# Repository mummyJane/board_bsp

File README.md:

# board_bsp

Board Support Packages (BSPs), test firmware, documentation and KiCad schematics
for a family of ESP32-P4 based boards.

Current version: see [VERSION](VERSION) · History: see [CHANGELOG.md](CHANGELOG.md)

## Boards

| Board | Folder | Status |
|-------|--------|--------|
| Waveshare ESP32-P4-WIFI6-Touch-LCD-7B-C (reference / test board) | [boards/esp32-p4-wifi6-touch-lcd-7b](boards/esp32-p4-wifi6-touch-lcd-7b/) | Bring-up |
| ADSB_Test — ESP32-P4 ADS-B test board derived from the above | [boards/adsb-test](boards/adsb-test/) | Rev A design (requirements / architecture) |

The Waveshare board is used to develop and validate the BSP and test code. The
next (custom) board reuses its design as a starting point, so everything proven
on the reference board should carry over with only pin/peripheral changes.

## Repository layout

```
board_bsp/
├── VERSION                 Project version (SemVer)
├── CHANGELOG.md            All notable changes, newest first
├── docs/                   Project-wide docs (setup, conventions)
├── common/components/      ESP-IDF components shared by all boards
└── boards/
    ├── _template/          Starting point for a new board
    └── <board>/
        ├── README.md       Board summary, pin map, status
        ├── bsp/            ESP-IDF BSP component for the board
        ├── test/           ESP-IDF test application (hardware bring-up tests)
        ├── docs/           Datasheets notes, bring-up logs, errata
        └── hardware/       KiCad project (schematic / PCB)
```

## Reference documents

Datasheets and links for every part: [docs/datasheets.md](docs/datasheets.md).
Run `python tools/fetch_datasheets.py` to download the PDFs into `datasheets/`
(git-ignored; vendor documents aren't redistributed in this public repo).

## Manufacturing

PCBs and assembly by PCBWay: capabilities, design rules and the hand-solder policy are in
[docs/pcb-manufacturing.md](docs/pcb-manufacturing.md).

## Toolchain

- **Firmware:** ESP-IDF v6.1 (ESP32-P4 target) — see [docs/setup.md](docs/setup.md)
- **Hardware:** KiCad 10

## Quick start (test app)

```powershell
. .\tools\idf_env.ps1     # load ESP-IDF v6.1
cd boards\esp32-p4-wifi6-touch-lcd-7b\test
idf.py set-target esp32p4
idf.py build flash monitor
```

## Versioning

See [docs/versioning.md](docs/versioning.md).

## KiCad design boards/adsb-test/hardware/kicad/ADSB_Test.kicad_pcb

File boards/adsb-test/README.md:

# ADSB_Test

ESP32-P4 based ADS-B test board, derived from the Waveshare
ESP32-P4-WIFI6-Touch-LCD-7B-C reference board. It is kept as close to the
reference board as possible, so firmware and circuits can be proven on the
reference board while ADSB_Test is designed.

**Hardware revision:** Rev A (design started 2026-10-09). **Status:** requirements / architecture draft.

## Features

- **OSPTEK ESP32-P4C5 Core** module: ESP32-P4 (rev v3) + ESP32-C5 (dual-band Wi-Fi 6 backup link over SDIO, esp_hosted, same wiring as the reference board's C6), 16 MB flash, 32 MB PSRAM, IPEX antenna; 1.0 mm stamp holes
- P4 RTC on the always-on backup supply (optional DS3231M, not fitted by default)
- **ADSBee m1421** dual-band ADS-B receiver (1090 MHz Mode S + 978 MHz UAT), RF front end copied from the ADSBee 1421 carrier
- 10/100 Ethernet (LAN8720A RMII PHY, HR911105A RJ45 MagJack)
- **User USB-C:** USB-PD sink (main power + charging) and a USB-UART to the P4 user UART
- **Dev USB-C:** one cable for all debug: P4 USB-Serial/JTAG, P4 + C5 UARTs with auto-reset (FT2232H), m1421 console + firmware upload (RP2040 with ADSBee 1421 Programmer firmware). m1421 JTAG on a J-Link header
- **USB-A host** (P4 USB 2.0 HS) to an external hub: 1 SDR (AIS etc.), 2 supported, 4 nice-to-have
- GNSS module with PPS
- ≈ 188 × 97 mm board (screen + 12 mm margins on the short edges) with the 7" EK79007 panel bonded to its top side (Waveshare stack-up, all parts on the bottom). 3D-printed plastic case, thicker long walls Digital connectors on one edge; GNSS and ADS-B SMA connectors on the opposite edge, with optional RF cans
- 2S1P 18650 Li-ion (≥ 1 h with everything running), buck-boost charger with power path
- Voltage + current monitoring on every rail (3 × PAC1954, 12 channels)
- Same 7" 1024×600 MIPI-DSI display and touch as the reference board
- microSD (kept from the reference board). Audio, CAN, RS485 and camera dropped
- Test points on every rail, and a 2×20 keyed header for the **Kingst LA5016** cable: 16 key digital signals + PWM outputs. Second row reserved for an LA5032

## Documents

| Doc | Content |
|-----|---------|
| [docs/requirements.md](docs/requirements.md) | Numbered requirements and how each is tested before hardware exists |
| [docs/architecture.md](docs/architecture.md) | Block diagram, power tree, monitor channel map, USB topology, GPIO budget, risks, proposed parts |
| [docs/open-questions.md](docs/open-questions.md) | Decisions waiting on an answer |
| [docs/test-plan.md](docs/test-plan.md) | Phase 1 (reference board + eval boards) and Phase 2 (ADSB_Test) tests |
| [docs/bringup-log.md](docs/bringup-log.md) | Test results |

## Folders

| Folder | Content |
|--------|---------|
| [bsp/](bsp/) | ESP-IDF BSP component. Pin map in [board_pins.h](bsp/include/bsp/board_pins.h) |
| [test/](test/) | Test app (Unity menu) |
| [hardware/kicad/](hardware/kicad/) | KiCad 10 project `ADSB_Test.kicad_pro`. One hierarchical sheet per block, each holding its design notes. Project library in [lib/](hardware/kicad/lib/) (m1421 symbol + footprint) |

## KiCad sheets

| Page | Sheet | Contents |
|------|-------|----------|
| 1 | Top level | — |
| 2 | Power Input | User USB-C, STUSB4500 PD sink, input protection |
| 3 | Charger Battery | BQ25798 2S charger, pack connector, VBACKUP |
| 4 | Power Rails | 5 V / 3V3 bucks, POWER switch, shunts, load switches |
| 5 | Power Monitor | 3 x PAC1954 |
| 6 | MCU Module | OSPTEK ESP32-P4C5 Core (ESP32-P4 + ESP32-C5) |
| 7 | RTC | DS3231M on VBACKUP (optional, DNP) |
| 8 | Ethernet | LAN8720A + HR911105A |
| 9 | USB User | CP2102N -> P4 UART1 |
| 10 | Dev USB Hub | Dev USB-C, USB2514B hub, 3V3_DEV regulator |
| 11 | USB Host | TPS259621 eFuse, USB-A |
| 12 | GPS | MAX-M10S, active antenna, SMA |
| 13 | Display Touch | Panel supplies (as reference board), LCD + touch FPCs |
| 14 | M1421 | ADSBee m1421, Dev Kit header, JTAG, RF combiner, SMA |
| 15 | Storage Misc | microSD, TCA6408A expander |
| 16 | Test Debug | LA5016 header, PWM pads, mounting holes |
| 17 | Dev UARTs | FT2232H (P4 + C5 consoles, auto-reset), UART buffers |
| 18 | Dev m1421 Programmer | RP2040 + flash (stock ADSBee Programmer), m1421 buffers, GPIO header |

All sheets are generated by the scripts in [hardware/gen/](hardware/gen/) (whole-project ERC: 0 violations).

**Bill of materials:** [hardware/bom/ADSB_Test_BOM.md](hardware/bom/ADSB_Test_BOM.md), with manufacturer part
numbers, DigiKey/LCSC codes and order links, plus a DigiKey upload file. Rebuild with
`python boards/adsb-test/hardware/bom/make_bom.py --boards N`.

## Hardware revisions

| Rev | Date | Changes |
|-----|------|---------|
| A | — | In design |

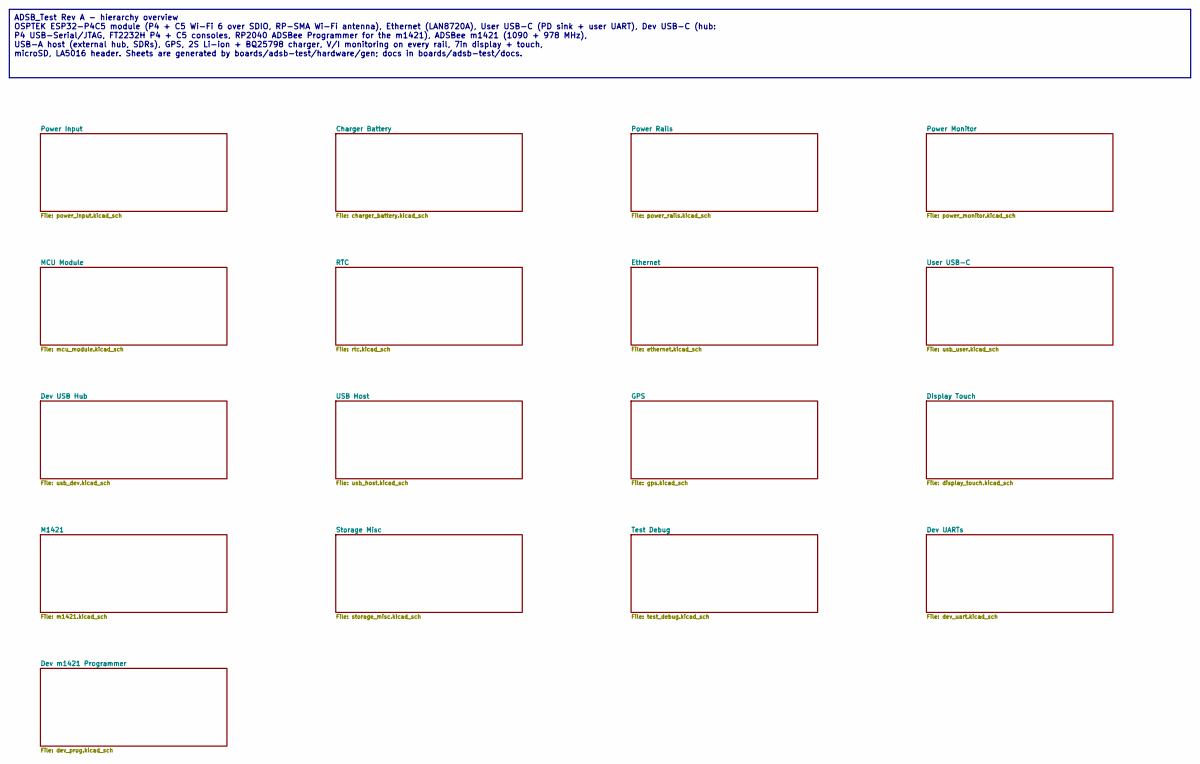
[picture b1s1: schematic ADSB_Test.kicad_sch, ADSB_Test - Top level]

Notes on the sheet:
ADSB_Test Rev A - hierarchy overview OSPTEK ESP32-P4C5 module (P4 + C5 Wi-Fi 6 over SDIO, RP-SMA Wi-Fi antenna), Ethernet (LAN8720A), User USB-C (PD sink + user UART), Dev USB-C (hub: P4 USB-Serial/JTAG, FT2232H P4 + C5 consoles, RP2040 ADSBee Programmer for the m1421), ADSBee m1421 (1090 + 978 MHz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

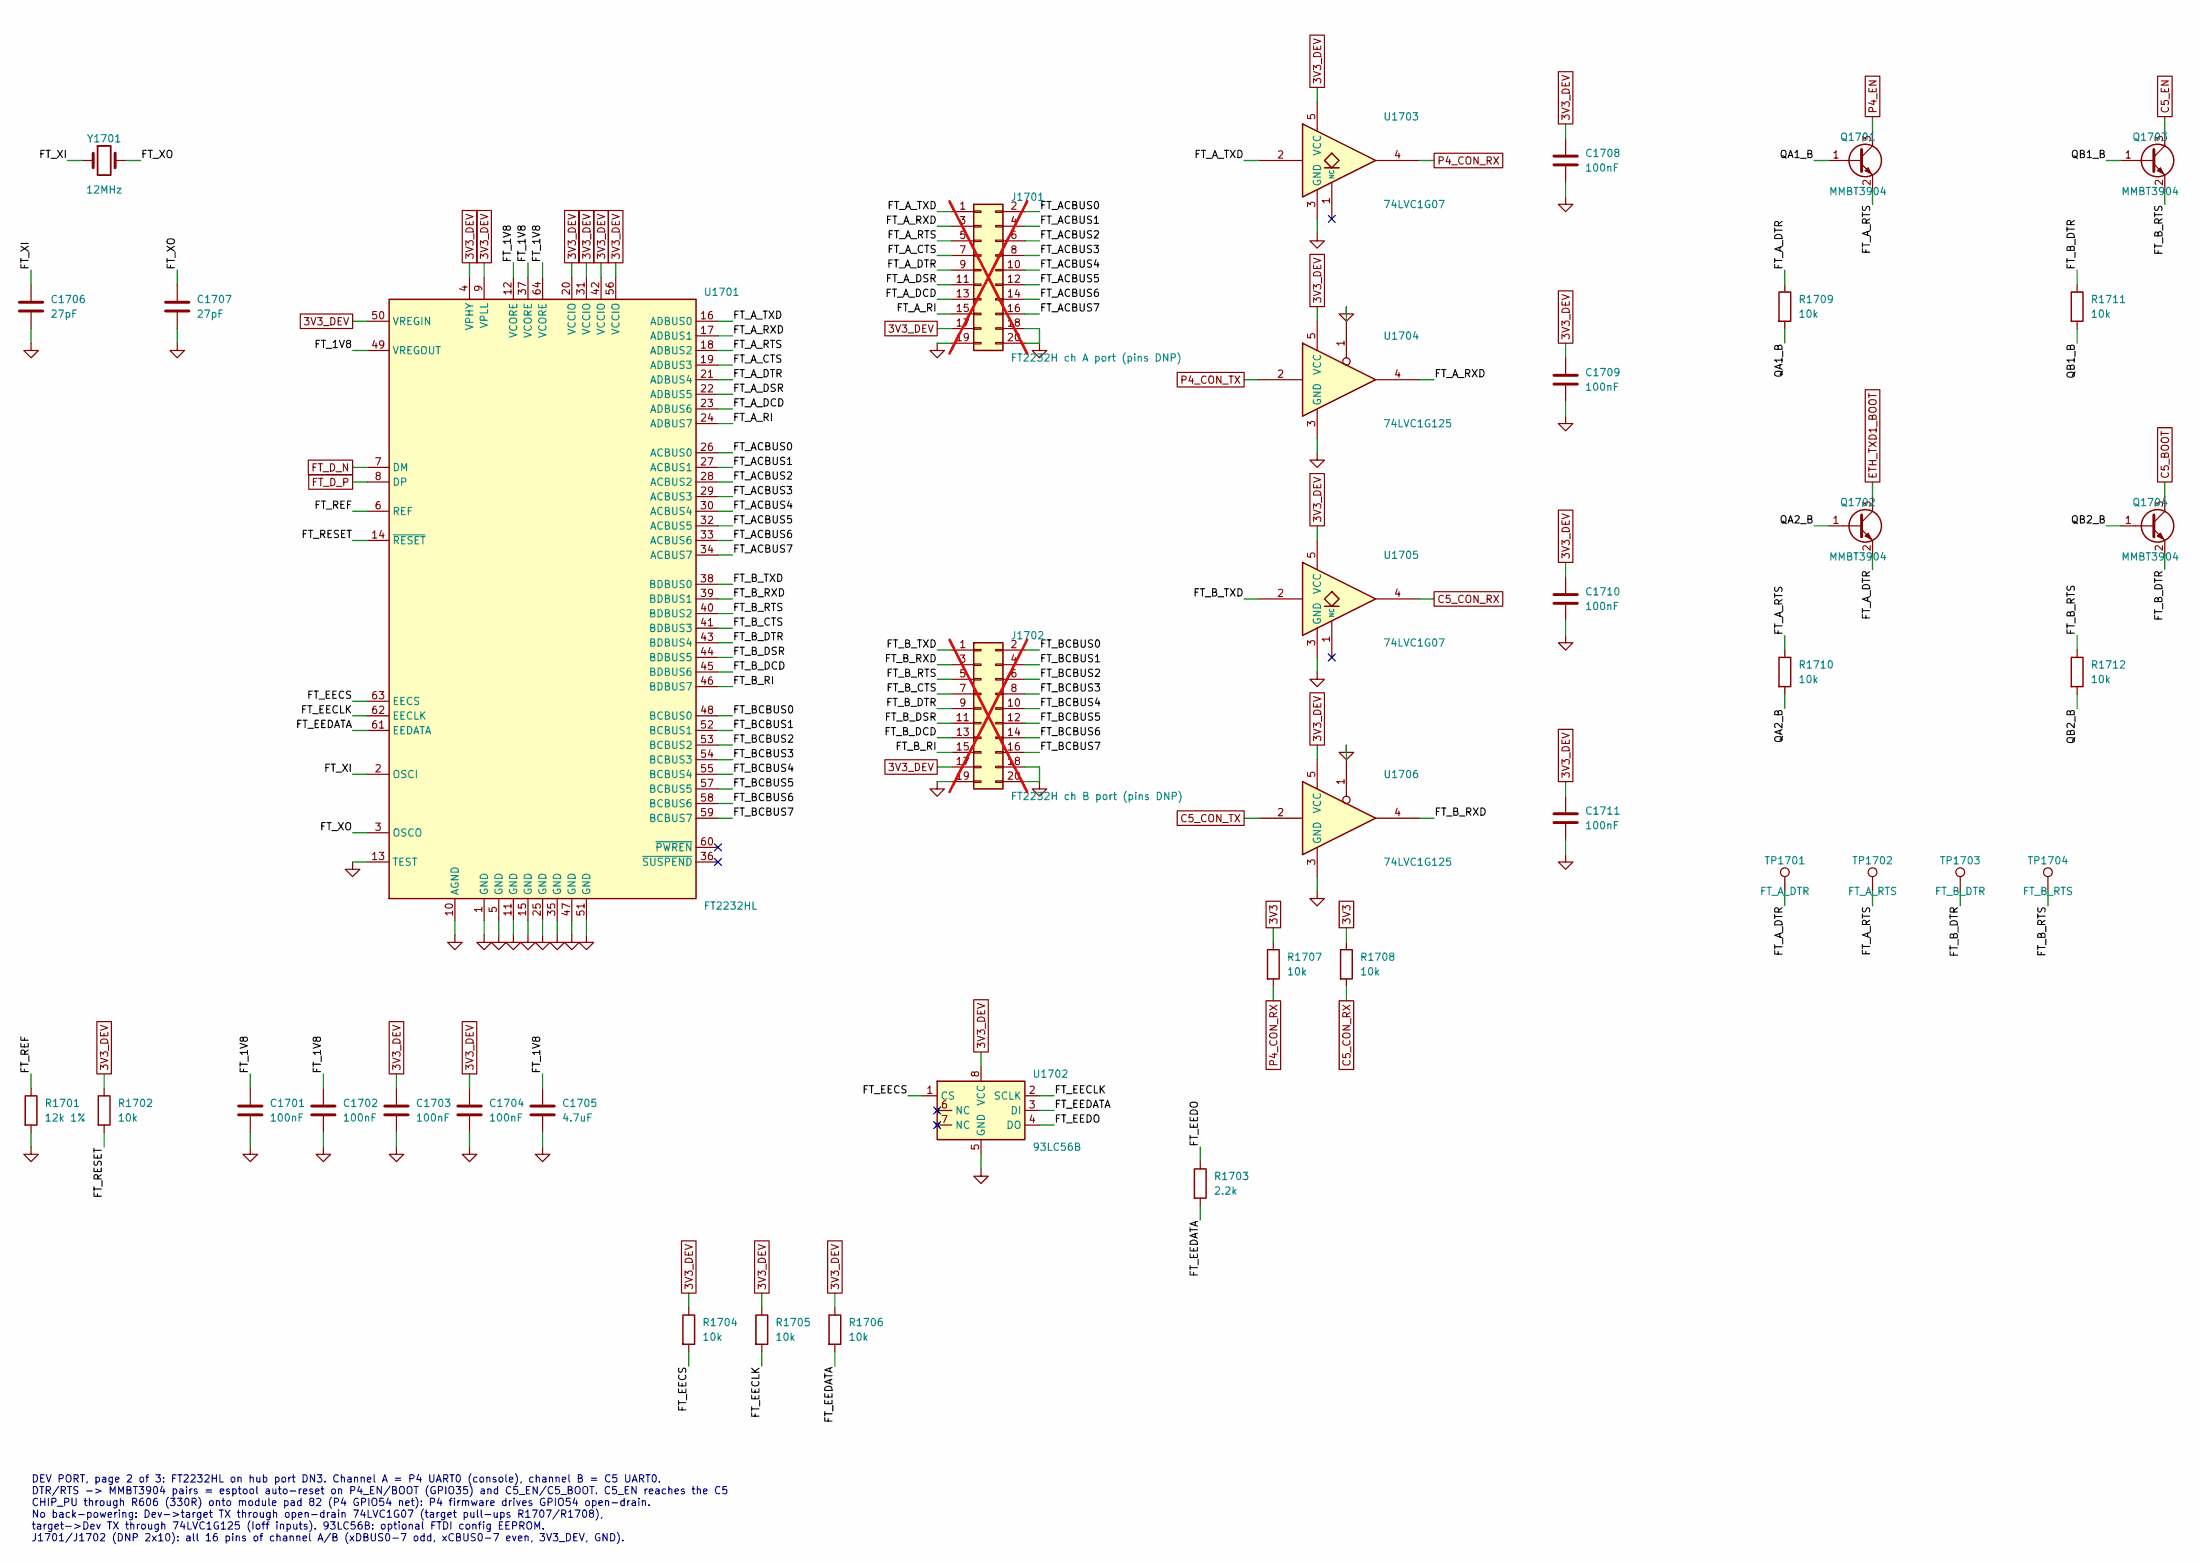
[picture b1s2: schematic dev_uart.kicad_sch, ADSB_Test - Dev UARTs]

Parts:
C1701, C1702, C1703, C1704, C1708, C1709, C1710, C1711: 100nF; C_0805_2012Metric_Pad1.18x1.45mm_HandSolder
C1705: 4.7uF; C_0805_2012Metric_Pad1.18x1.45mm_HandSolder
C1706, C1707: 27pF; C_0805_2012Metric_Pad1.18x1.45mm_HandSolder
J1701: FT2232H ch A port (pins DNP); PinHeader_2x10_P2.54mm_Vertical; not fitted
J1702: FT2232H ch B port (pins DNP); PinHeader_2x10_P2.54mm_Vertical; not fitted
Q1701, Q1702, Q1703, Q1704: MMBT3904; SOT-23_Handsoldering
R1701: 12k 1%; R_0805_2012Metric_Pad1.20x1.40mm_HandSolder
R1702, R1704, R1705, R1706, R1707, R1708, R1709, R1710, R1711, R1712: 10k; R_0805_2012Metric_Pad1.20x1.40mm_HandSolder
R1703: 2.2k; R_0805_2012Metric_Pad1.20x1.40mm_HandSolder
TP1701: FT_A_DTR; TestPoint_Pad_D1.5mm
TP1702: FT_A_RTS; TestPoint_Pad_D1.5mm
TP1703: FT_B_DTR; TestPoint_Pad_D1.5mm
TP1704: FT_B_RTS; TestPoint_Pad_D1.5mm
U1701: FT2232HL; LQFP-64_10x10mm_P0.5mm
U1702: 93LC56B; SOIC-8_3.9x4.9mm_P1.27mm
U1703, U1705: 74LVC1G07; SOT-23-5_HandSoldering
U1704, U1706: 74LVC1G125; SOT-23-5_HandSoldering
Y1701: 12MHz; Crystal_SMD_5032-2Pin_5.0x3.2mm_HandSoldering

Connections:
3V3: R1707.1, R1708.1; also elsewhere on the board
3V3_DEV: C1703.1, C1704.1, C1708.1, C1709.1, C1710.1, C1711.1, J1701.17, J1702.17, R1702.1, R1704.1, R1705.1, R1706.1, U1701.4 (VPHY), U1701.9 (VPLL), U1701.20 (VCCIO), U1701.31 (VCCIO), U1701.42 (VCCIO), U1701.50 (VREGIN), U1701.56 (VCCIO), U1702.8 (VCC), U1703.5 (VCC), U1704.5 (VCC), U1705.5 (VCC), U1706.5 (VCC); also elsewhere on the board
/Dev UARTs/FT_1V8: C1701.1, C1702.1, C1705.1, U1701.12 (VCORE), U1701.37 (VCORE), U1701.49 (VREGOUT), U1701.64 (VCORE)
/Dev UARTs/FT_ACBUS0: J1701.2, U1701.26 (ACBUS0)
/Dev UARTs/FT_ACBUS1: J1701.4, U1701.27 (ACBUS1)
/Dev UARTs/FT_ACBUS2: J1701.6, U1701.28 (ACBUS2)
/Dev UARTs/FT_ACBUS3: J1701.8, U1701.29 (ACBUS3)
/Dev UARTs/FT_ACBUS4: J1701.10, U1701.30 (ACBUS4)
/Dev UARTs/FT_ACBUS5: J1701.12, U1701.32 (ACBUS5)
/Dev UARTs/FT_ACBUS6: J1701.14, U1701.33 (ACBUS6)
/Dev UARTs/FT_ACBUS7: J1701.16, U1701.34 (ACBUS7)
/Dev UARTs/FT_A_CTS: J1701.7, U1701.19 (ADBUS3)
/Dev UARTs/FT_A_DCD: J1701.13, U1701.23 (ADBUS6)
/Dev UARTs/FT_A_DSR: J1701.11, U1701.22 (ADBUS5)
/Dev UARTs/FT_A_DTR: J1701.9, Q1702.2 (E), R1709.1, TP1701.1, U1701.21 (ADBUS4)
/Dev UARTs/FT_A_RI: J1701.15, U1701.24 (ADBUS7)
/Dev UARTs/FT_A_RTS: J1701.5, Q1701.2 (E), R1710.1, TP1702.1, U1701.18 (ADBUS2)
/Dev UARTs/FT_A_RXD: J1701.3, U1701.17 (ADBUS1), U1704.4
/Dev UARTs/FT_A_TXD: J1701.1, U1701.16 (ADBUS0), U1703.2
/Dev UARTs/FT_BCBUS0: J1702.2, U1701.48 (BCBUS0)
/Dev UARTs/FT_BCBUS1: J1702.4, U1701.52 (BCBUS1)
/Dev UARTs/FT_BCBUS2: J1702.6, U1701.53 (BCBUS2)
/Dev UARTs/FT_BCBUS3: J1702.8, U1701.54 (BCBUS3)
/Dev UARTs/FT_BCBUS4: J1702.10, U1701.55 (BCBUS4)
/Dev UARTs/FT_BCBUS5: J1702.12, U1701.57 (BCBUS5)
/Dev UARTs/FT_BCBUS6: J1702.14, U1701.58 (BCBUS6)
/Dev UARTs/FT_BCBUS7: J1702.16, U1701.59 (BCBUS7)
/Dev UARTs/FT_B_CTS: J1702.7, U1701.41 (BDBUS3)
/Dev UARTs/FT_B_DCD: J1702.13, U1701.45 (BDBUS6)
/Dev UARTs/FT_B_DSR: J1702.11, U1701.44 (BDBUS5)
/Dev UARTs/FT_B_DTR: J1702.9, Q1704.2 (E), R1711.1, TP1703.1, U1701.43 (BDBUS4)
/Dev UARTs/FT_B_RI: J1702.15, U1701.46 (BDBUS7)
/Dev UARTs/FT_B_RTS: J1702.5, Q1703.2 (E), R1712.1, TP1704.1, U1701.40 (BDBUS2)
/Dev UARTs/FT_B_RXD: J1702.3, U1701.39 (BDBUS1), U1706.4
/Dev UARTs/FT_B_TXD: J1702.1, U1701.38 (BDBUS0), U1705.2
/Dev UARTs/FT_EECLK: R1705.2, U1701.62 (EECLK), U1702.2 (SCLK)
/Dev UARTs/FT_EECS: R1704.2, U1701.63 (EECS), U1702.1 (CS)
/Dev UARTs/FT_EEDATA: R1703.2, R1706.2, U1701.61 (EEDATA), U1702.3 (DI)
/Dev UARTs/FT_EEDO: R1703.1, U1702.4 (DO)
/Dev UARTs/FT_REF: R1701.1, U1701.6 (REF)
/Dev UARTs/FT_RESET: R1702.2, U1701.14 (~RESET)
/Dev UARTs/FT_XI: C1706.1, U1701.2 (OSCI), Y1701.1
/Dev UARTs/FT_XO: C1707.1, U1701.3 (OSCO), Y1701.2
/Dev UARTs/QA1_B: Q1701.1 (B), R1709.2
/Dev UARTs/QA2_B: Q1702.1 (B), R1710.2
/Dev UARTs/QB1_B: Q1703.1 (B), R1711.2
/Dev UARTs/QB2_B: Q1704.1 (B), R1712.2
C5_BOOT: Q1704.3 (C); also elsewhere on the board
C5_CON_RX: R1708.2, U1705.4; also elsewhere on the board
C5_CON_TX: U1706.2; also elsewhere on the board
C5_EN: Q1703.3 (C); also elsewhere on the board
ETH_TXD1_BOOT: Q1702.3 (C); also elsewhere on the board
FT_D_N: U1701.7 (DM); also elsewhere on the board
FT_D_P: U1701.8 (DP); also elsewhere on the board
GND: C1701.2, C1702.2, C1703.2, C1704.2, C1705.2, C1706.2, C1707.2, C1708.2, C1709.2, C1710.2, C1711.2, J1701.18, J1701.19, J1701.20, J1702.18, J1702.19, J1702.20, R1701.2, U1701.1 (GND), U1701.5 (GND), U1701.10 (AGND), U1701.11 (GND), U1701.13 (TEST), U1701.15 (GND), U1701.25 (GND), U1701.35 (GND), U1701.47 (GND), U1701.51 (GND), U1702.5 (GND), U1703.3 (GND), U1704.1, U1704.3 (GND), U1705.3 (GND), U1706.1, U1706.3 (GND); also elsewhere on the board
P4_CON_RX: R1707.2, U1703.4; also elsewhere on the board
P4_CON_TX: U1704.2; also elsewhere on the board
P4_EN: Q1701.3 (C); also elsewhere on the board

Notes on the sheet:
DEV PORT, page 2 of 3: FT2232HL on hub port DN3. Channel A = P4 UART0 (console), channel B = C5 UART0. DTR/RTS -> MMBT3904 pairs = esptool auto-reset on P4_EN/BOOT (GPIO35) and C5_EN/C5_BOOT. C5_EN reaches the C5 CHIP_PU through R606 (330R) onto module pad 82 (P4 GPIO54 net): P4 firmware drives GPI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

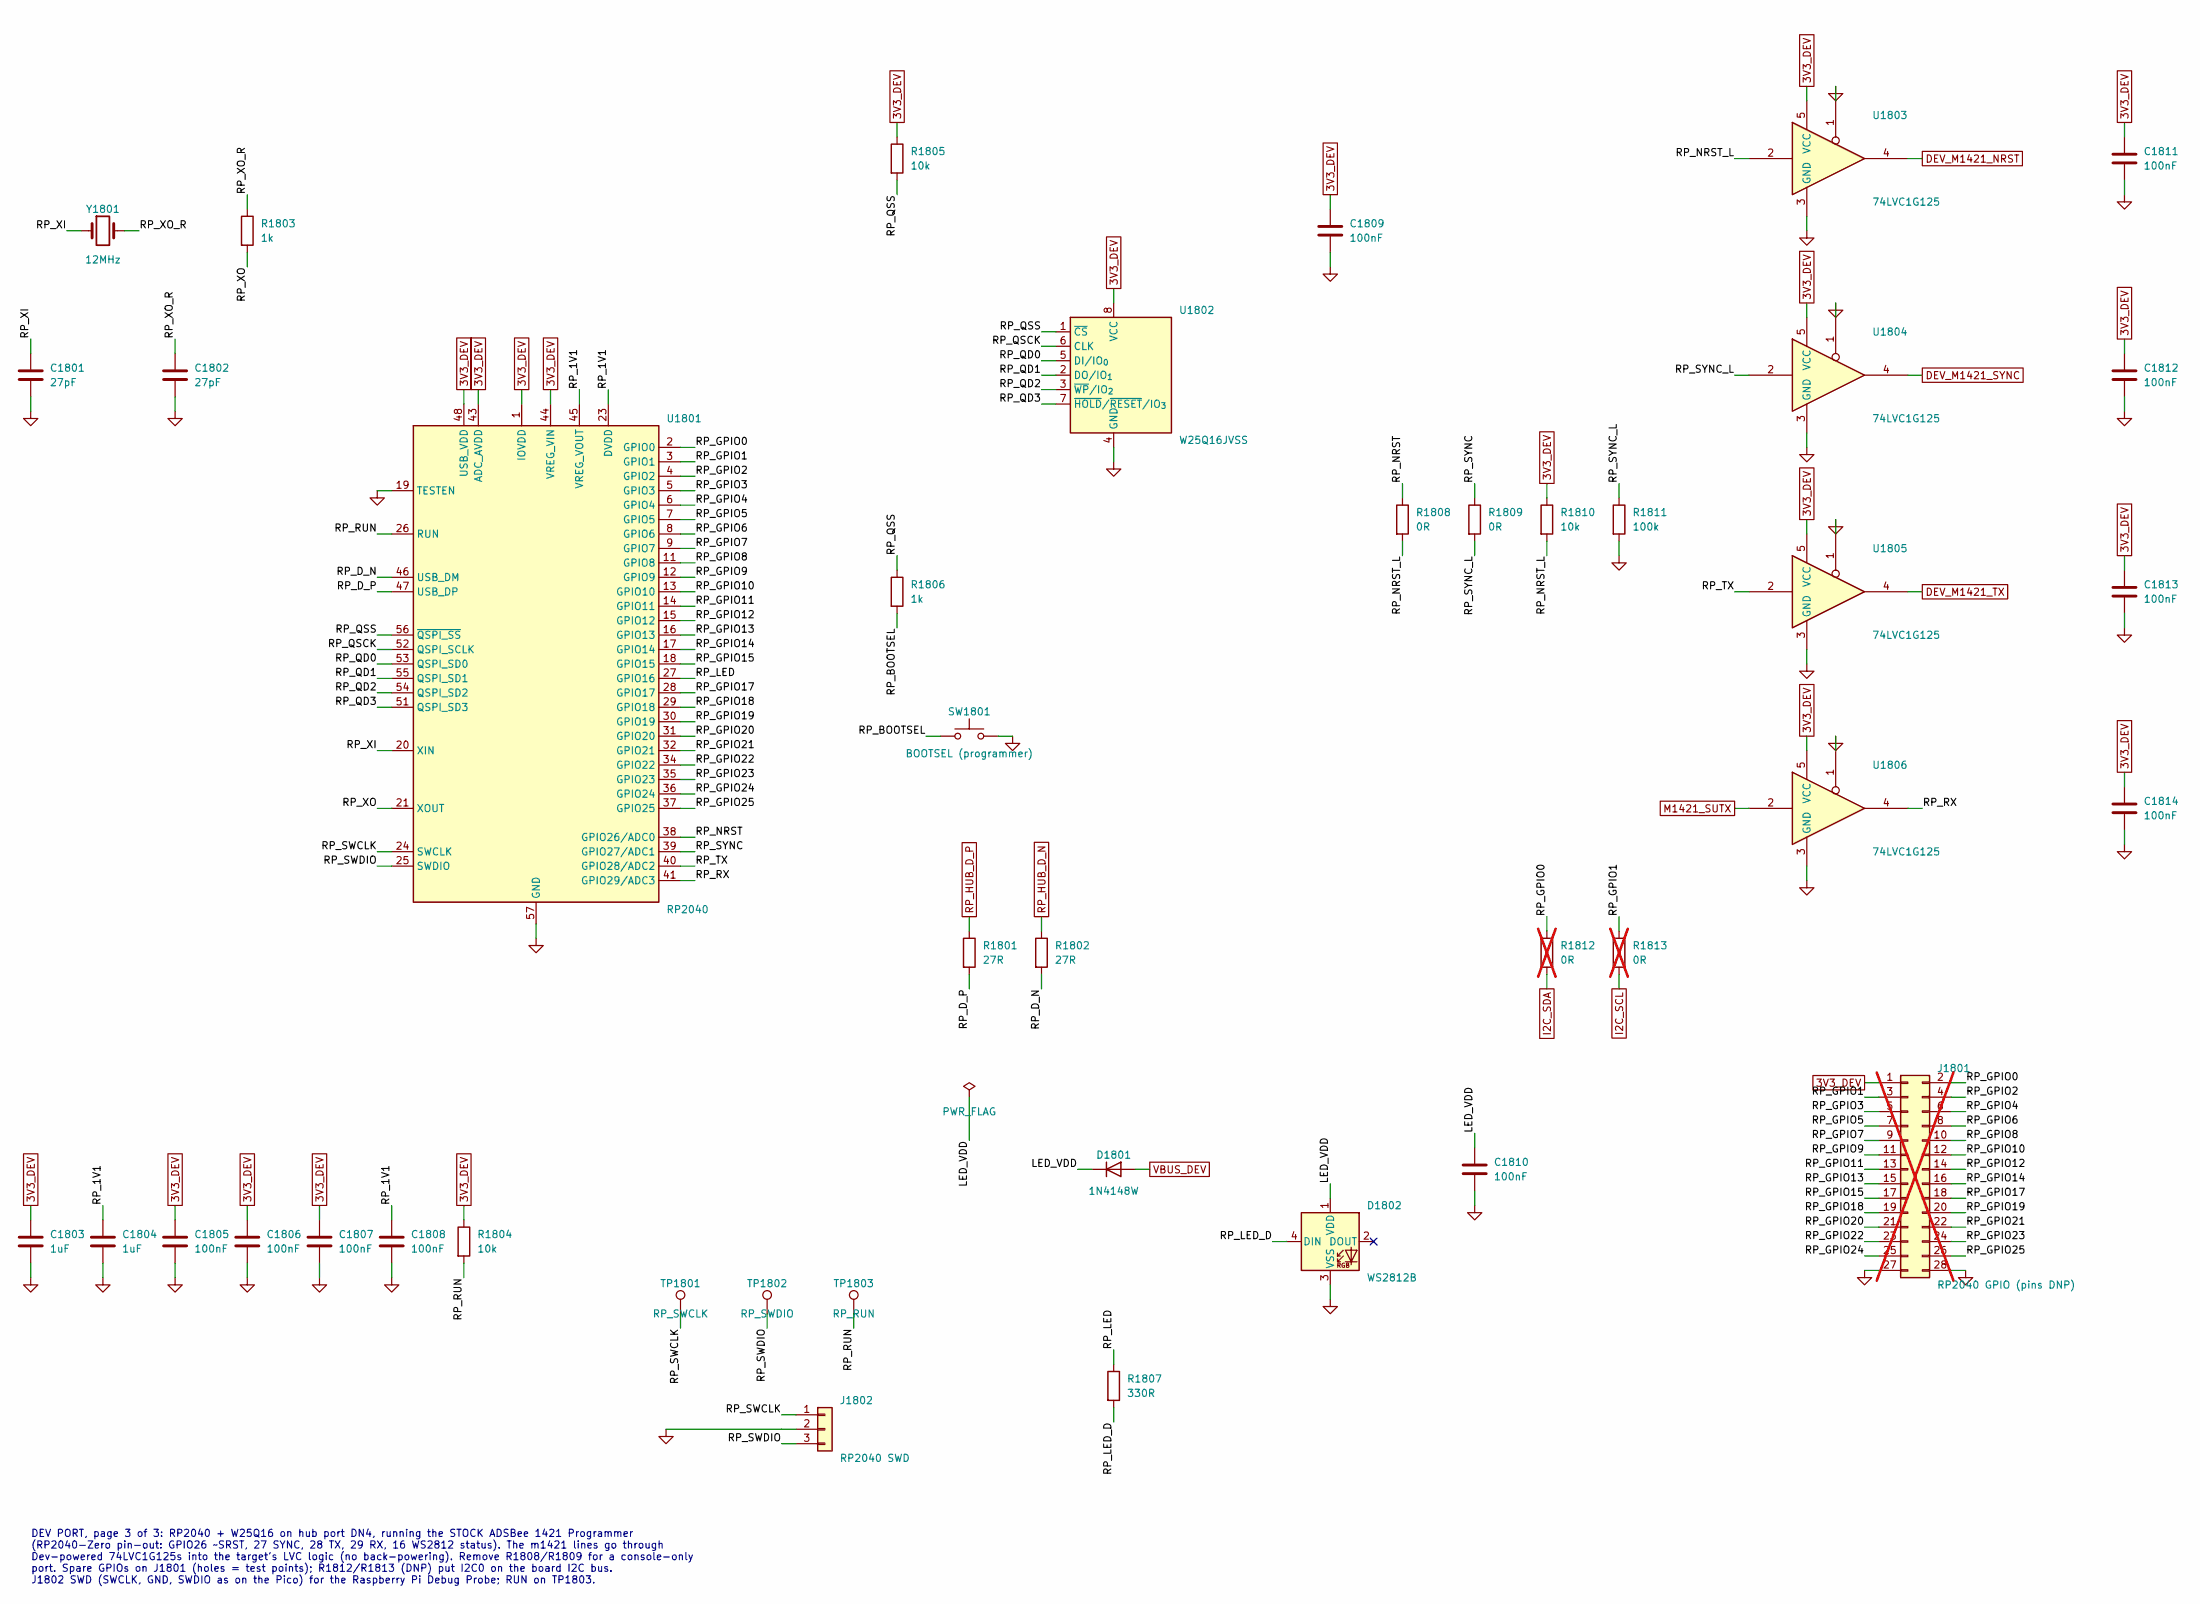
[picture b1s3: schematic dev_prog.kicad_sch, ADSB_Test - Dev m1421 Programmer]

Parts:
C1801, C1802: 27pF; C_0805_2012Metric_Pad1.18x1.45mm_HandSolder
C1803, C1804: 1uF; C_0805_2012Metric_Pad1.18x1.45mm_HandSolder
C1805, C1806, C1807, C1808, C1809, C1810, C1811, C1812, C1813, C1814: 100nF; C_0805_2012Metric_Pad1.18x1.45mm_HandSolder
D1801: 1N4148W; D_SOD-123
D1802: WS2812B; LED_WS2812B_PLCC4_5.0x5.0mm_P3.2mm
J1801: RP2040 GPIO (pins DNP); PinHeader_2x14_P2.54mm_Vertical; not fitted
J1802: RP2040 SWD; PinHeader_1x03_P2.54mm_Vertical
R1801, R1802: 27R; R_0805_2012Metric_Pad1.20x1.40mm_HandSolder
R1803, R1806: 1k; R_0805_2012Metric_Pad1.20x1.40mm_HandSolder
R1804, R1805, R1810: 10k; R_0805_2012Metric_Pad1.20x1.40mm_HandSolder
R1807: 330R; R_0805_2012Metric_Pad1.20x1.40mm_HandSolder
R1808, R1809: 0R; R_0805_2012Metric_Pad1.20x1.40mm_HandSolder
R1811: 100k; R_0805_2012Metric_Pad1.20x1.40mm_HandSolder
R1812, R1813: 0R; R_0805_2012Metric_Pad1.20x1.40mm_HandSolder; not fitted
SW1801: BOOTSEL (programmer); SW_PUSH_6mm
TP1801: RP_SWCLK; TestPoint_Pad_D1.5mm
TP1802: RP_SWDIO; TestPoint_Pad_D1.5mm
TP1803: RP_RUN; TestPoint_Pad_D1.5mm
U1801: RP2040; QFN-56-1EP_7x7mm_P0.4mm_EP3.2x3.2mm_HandSolder
U1802: W25Q16JVSS; SOIC-8_5.3x5.3mm_P1.27mm
U1803, U1804, U1805, U1806: 74LVC1G125; SOT-23-5_HandSoldering
Y1801: 12MHz; Crystal_SMD_5032-2Pin_5.0x3.2mm_HandSoldering

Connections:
3V3_DEV: C1803.1, C1805.1, C1806.1, C1807.1, C1809.1, C1811.1, C1812.1, C1813.1, C1814.1, J1801.1, R1804.1, R1805.1, R1810.1, U1801.1 (IOVDD), U1801.10 (IOVDD), U1801.22 (IOVDD), U1801.33 (IOVDD), U1801.42 (IOVDD), U1801.43 (ADC_AVDD), U1801.44 (VREG_VIN), U1801.48 (USB_VDD), U1801.49 (IOVDD), U1802.8 (VCC), U1803.5 (VCC), U1804.5 (VCC), U1805.5 (VCC), U1806.5 (VCC); also elsewhere on the board
/Dev m1421 Programmer/LED_VDD: C1810.1, D1801.1 (K), D1802.1 (VDD)
/Dev m1421 Programmer/RP_1V1: C1804.1, C1808.1, U1801.23 (DVDD), U1801.45 (VREG_VOUT), U1801.50 (DVDD)
/Dev m1421 Programmer/RP_BOOTSEL: R1806.2, SW1801.1
/Dev m1421 Programmer/RP_D_N: R1802.2, U1801.46 (USB_DM)
/Dev m1421 Programmer/RP_D_P: R1801.2, U1801.47 (USB_DP)
/Dev m1421 Programmer/RP_GPIO0: J1801.2, R1812.1, U1801.2 (GPIO0)
/Dev m1421 Programmer/RP_GPIO1: J1801.3, R1813.1, U1801.3 (GPIO1)
/Dev m1421 Programmer/RP_GPIO2: J1801.4, U1801.4 (GPIO2)
/Dev m1421 Programmer/RP_GPIO3: J1801.5, U1801.5 (GPIO3)
/Dev m1421 Programmer/RP_GPIO4: J1801.6, U1801.6 (GPIO4)
/Dev m1421 Programmer/RP_GPIO5: J1801.7, U1801.7 (GPIO5)
/Dev m1421 Programmer/RP_GPIO6: J1801.8, U1801.8 (GPIO6)
/Dev m1421 Programmer/RP_GPIO7: J1801.9, U1801.9 (GPIO7)
/Dev m1421 Programmer/RP_GPIO8: J1801.10, U1801.11 (GPIO8)
/Dev m1421 Programmer/RP_GPIO9: J1801.11, U1801.12 (GPIO9)
/Dev m1421 Programmer/RP_GPIO10: J1801.12, U1801.13 (GPIO10)
/Dev m1421 Programmer/RP_GPIO11: J1801.13, U1801.14 (GPIO11)
/Dev m1421 Programmer/RP_GPIO12: J1801.14, U1801.15 (GPIO12)
/Dev m1421 Programmer/RP_GPIO13: J1801.15, U1801.16 (GPIO13)
/Dev m1421 Programmer/RP_GPIO14: J1801.16, U1801.17 (GPIO14)
/Dev m1421 Programmer/RP_GPIO15: J1801.17, U1801.18 (GPIO15)
/Dev m1421 Programmer/RP_GPIO17: J1801.18, U1801.28 (GPIO17)
/Dev m1421 Programmer/RP_GPIO18: J1801.19, U1801.29 (GPIO18)
/Dev m1421 Programmer/RP_GPIO19: J1801.20, U1801.30 (GPIO19)
/Dev m1421 Programmer/RP_GPIO20: J1801.21, U1801.31 (GPIO20)
/Dev m1421 Programmer/RP_GPIO21: J1801.22, U1801.32 (GPIO21)
/Dev m1421 Programmer/RP_GPIO22: J1801.23, U1801.34 (GPIO22)
/Dev m1421 Programmer/RP_GPIO23: J1801.24, U1801.35 (GPIO23)
/Dev m1421 Programmer/RP_GPIO24: J1801.25, U1801.36 (GPIO24)
/Dev m1421 Programmer/RP_GPIO25: J1801.26, U1801.37 (GPIO25)
/Dev m1421 Programmer/RP_LED: R1807.1, U1801.27 (GPIO16)
/Dev m1421 Programmer/RP_LED_D: D1802.4 (DIN), R1807.2
/Dev m1421 Programmer/RP_NRST: R1808.1, U1801.38 (GPIO26/ADC0)
/Dev m1421 Programmer/RP_NRST_L: R1808.2, R1810.2, U1803.2
/Dev m1421 Programmer/RP_QD0: U1801.53 (QSPI_SD0), U1802.5 (DI/IO_{0})
/Dev m1421 Programmer/RP_QD1: U1801.55 (QSPI_SD1), U1802.2 (DO/IO_{1})
/Dev m1421 Programmer/RP_QD2: U1801.54 (QSPI_SD2), U1802.3 (~WP/IO_{2})
/Dev m1421 Programmer/RP_QD3: U1801.51 (QSPI_SD3), U1802.7 (~HOLD/~RESET/IO_{3})
/Dev m1421 Programmer/RP_QSCK: U1801.52 (QSPI_SCLK), U1802.6 (CLK)
/Dev m1421 Programmer/RP_QSS: R1805.2, R1806.1, U1801.56 (~QSPI_SS), U1802.1 (~CS)
/Dev m1421 Programmer/RP_RUN: R1804.2, TP1803.1, U1801.26 (RUN)
/Dev m1421 Programmer/RP_RX: U1801.41 (GPIO29/ADC3), U1806.4
/Dev m1421 Programmer/RP_SWCLK: J1802.1, TP1801.1, U1801.24 (SWCLK)
/Dev m1421 Programmer/RP_SWDIO: J1802.3, TP1802.1, U1801.25 (SWDIO)
/Dev m1421 Programmer/RP_SYNC: R1809.1, U1801.39 (GPIO27/ADC1)
/Dev m1421 Programmer/RP_SYNC_L: R1809.2, R1811.1, U1804.2
/Dev m1421 Programmer/RP_TX: U1801.40 (GPIO28/ADC2), U1805.2
/Dev m1421 Programmer/RP_XI: C1801.1, U1801.20 (XIN), Y1801.1
/Dev m1421 Programmer/RP_XO: R1803.2, U1801.21 (XOUT)
/Dev m1421 Programmer/RP_XO_R: C1802.1, R1803.1, Y1801.2
DEV_M1421_NRST: U1803.4; also elsewhere on the board
DEV_M1421_SYNC: U1804.4; also elsewhere on the board
DEV_M1421_TX: U1805.4; also elsewhere on the board
GND: C1801.2, C1802.2, C1803.2, C1804.2, C1805.2, C1806.2, C1807.2, C1808.2, C1809.2, C1810.2, C1811.2, C1812.2, C1813.2, C1814.2, D1802.3 (VSS), J1801.27, J1801.28, J1802.2, R1811.2, SW1801.2, U1801.19 (TESTEN), U1801.57 (GND), U1802.4 (GND), U1803.1, U1803.3 (GND), U1804.1, U1804.3 (GND), U1805.1, U1805.3 (GND), U1806.1, U1806.3 (GND); also elsewhere on the board
I2C_SCL: R1813.2; also elsewhere on the board
I2C_SDA: R1812.2; also elsewhere on the board
M1421_SUTX: U1806.2; also elsewhere on the board
RP_HUB_D_N: R1802.1; also elsewhere on the board
RP_HUB_D_P: R1801.1; also elsewhere on the board
VBUS_DEV: D1801.2 (A); also elsewhere on the board

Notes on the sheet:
DEV PORT, page 3 of 3: RP2040 + W25Q16 on hub port DN4, running the STOCK ADSBee 1421 Programmer (RP2040-Zero pin-out: GPIO26 ~SRST, 27 SYNC, 28 TX, 29 RX, 16 WS2812 status). The m1421 lines go through Dev-powered 74LVC1G125s into the target's LVC logic (no back-powering). Remove R1808/R1809 for a 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

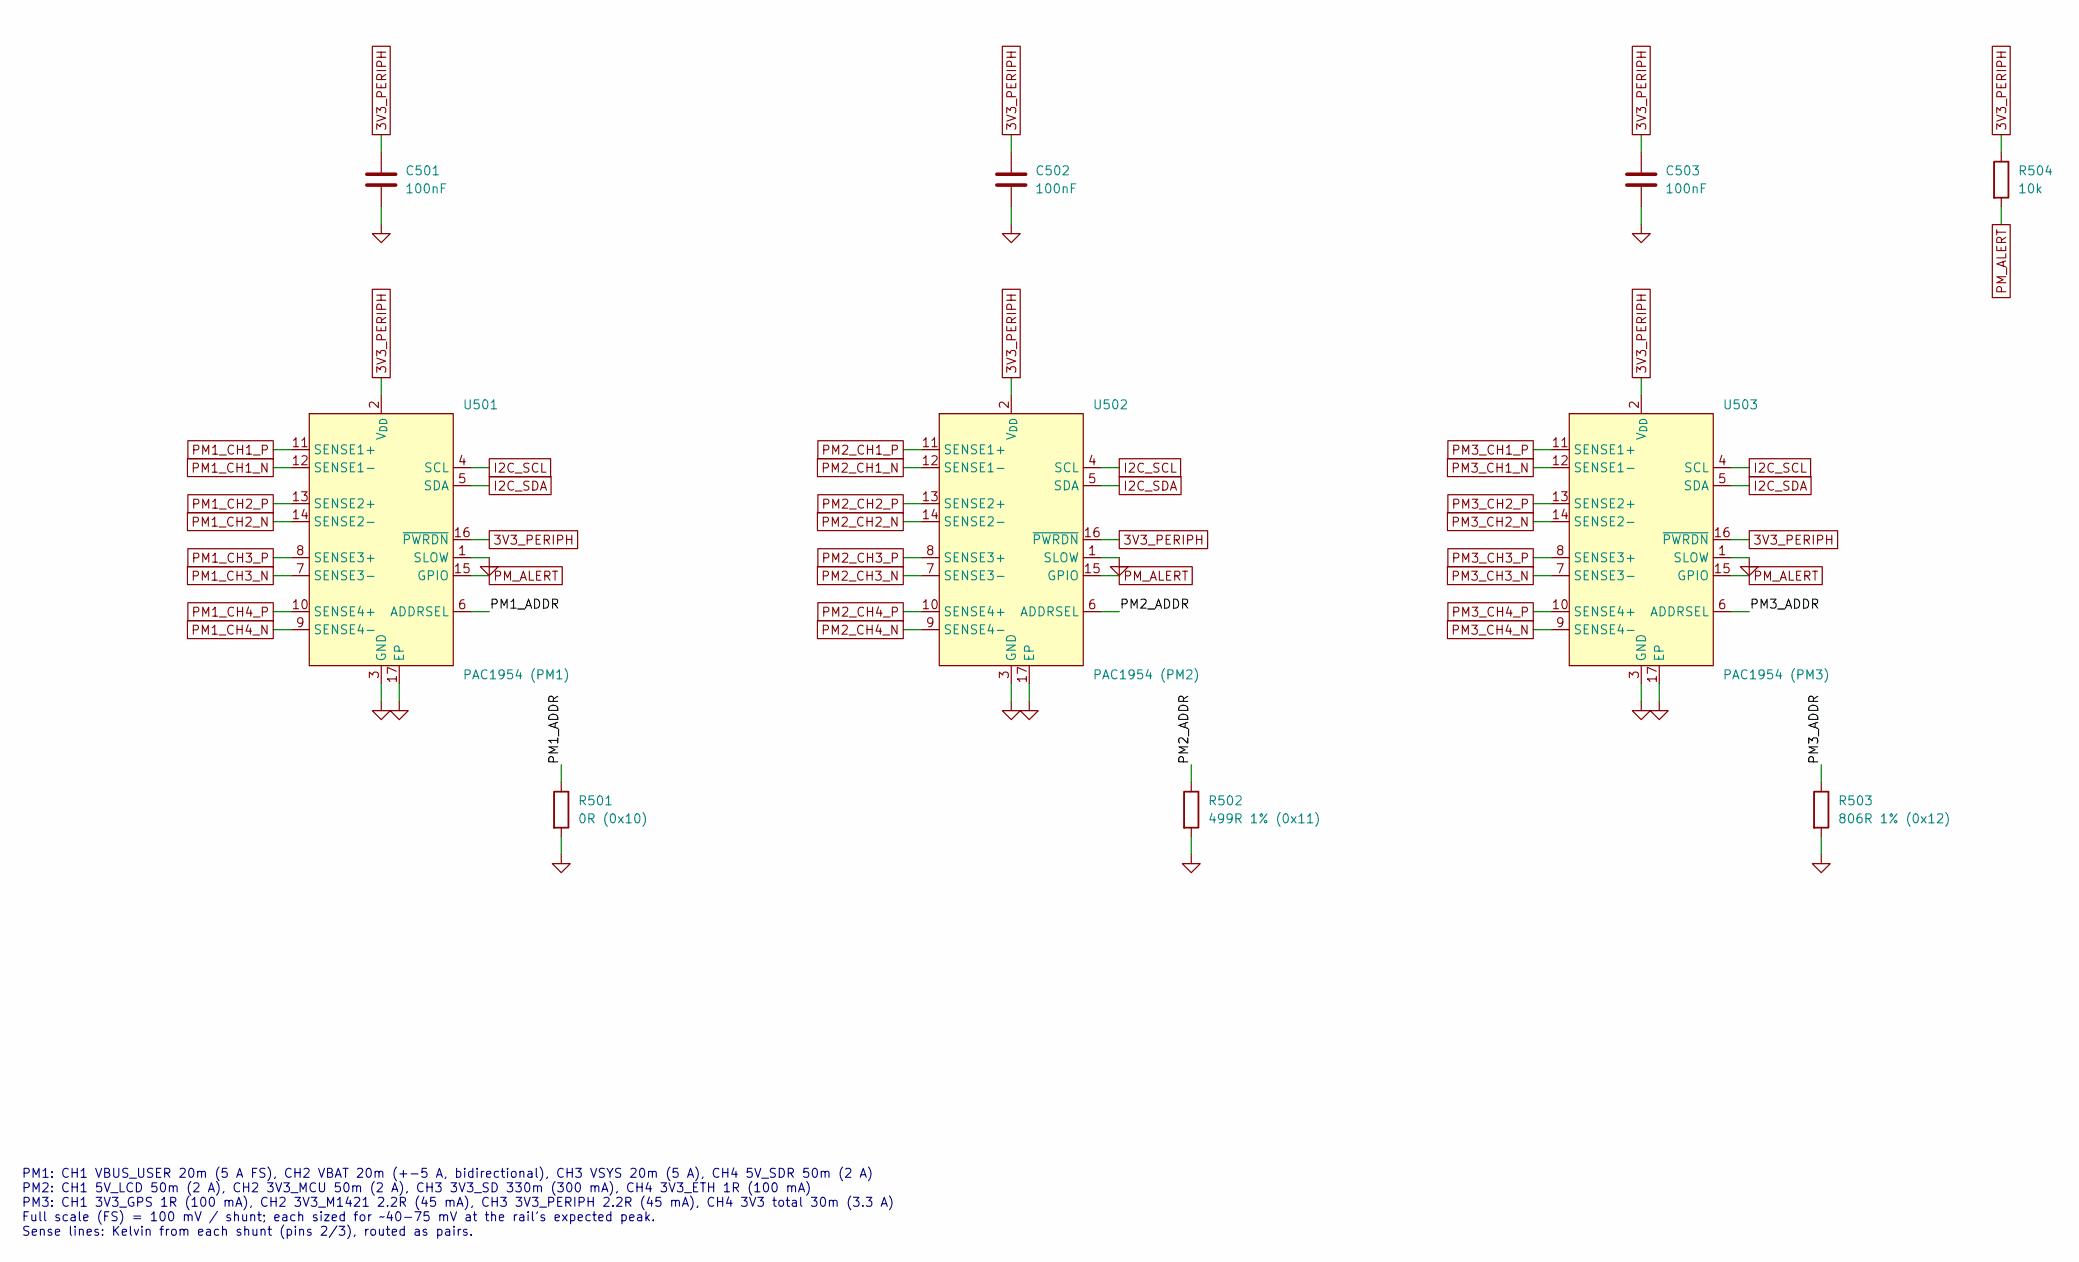
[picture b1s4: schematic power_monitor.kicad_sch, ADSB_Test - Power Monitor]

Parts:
C501, C502, C503: 100nF; C_0805_2012Metric_Pad1.18x1.45mm_HandSolder
R501: 0R (0x10); R_0805_2012Metric_Pad1.20x1.40mm_HandSolder
R502: 499R 1% (0x11); R_0805_2012Metric_Pad1.20x1.40mm_HandSolder
R503: 806R 1% (0x12); R_0805_2012Metric_Pad1.20x1.40mm_HandSolder
R504: 10k; R_0805_2012Metric_Pad1.20x1.40mm_HandSolder
U501: PAC1954 (PM1); VQFN-16-1EP_3x3mm_P0.5mm_EP1.1x1.1mm_HandSolder
U502: PAC1954 (PM2); VQFN-16-1EP_3x3mm_P0.5mm_EP1.1x1.1mm_HandSolder
U503: PAC1954 (PM3); VQFN-16-1EP_3x3mm_P0.5mm_EP1.1x1.1mm_HandSolder

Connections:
3V3_PERIPH: C501.1, C502.1, C503.1, R504.1, U501.2 (V_{DD}), U501.16 (~PWRDN), U502.2 (V_{DD}), U502.16 (~PWRDN), U503.2 (V_{DD}), U503.16 (~PWRDN); also elsewhere on the board
/Power Monitor/PM1_ADDR: R501.1, U501.6 (ADDRSEL)
/Power Monitor/PM2_ADDR: R502.1, U502.6 (ADDRSEL)
/Power Monitor/PM3_ADDR: R503.1, U503.6 (ADDRSEL)
GND: C501.2, C502.2, C503.2, R501.2, R502.2, R503.2, U501.1 (SLOW), U501.3 (GND), U501.17 (EP), U502.1 (SLOW), U502.3 (GND), U502.17 (EP), U503.1 (SLOW), U503.3 (GND), U503.17 (EP); also elsewhere on the board
I2C_SCL: U501.4 (SCL), U502.4 (SCL), U503.4 (SCL); also elsewhere on the board
I2C_SDA: U501.5 (SDA), U502.5 (SDA), U503.5 (SDA); also elsewhere on the board
PM1_CH1_N: U501.12 (SENSE1-); also elsewhere on the board
PM1_CH1_P: U501.11 (SENSE1+); also elsewhere on the board
PM1_CH2_N: U501.14 (SENSE2-); also elsewhere on the board
PM1_CH2_P: U501.13 (SENSE2+); also elsewhere on the board
PM1_CH3_N: U501.7 (SENSE3-); also elsewhere on the board
PM1_CH3_P: U501.8 (SENSE3+); also elsewhere on the board
PM1_CH4_N: U501.9 (SENSE4-); also elsewhere on the board
PM1_CH4_P: U501.10 (SENSE4+); also elsewhere on the board
PM2_CH1_N: U502.12 (SENSE1-); also elsewhere on the board
PM2_CH1_P: U502.11 (SENSE1+); also elsewhere on the board
PM2_CH2_N: U502.14 (SENSE2-); also elsewhere on the board
PM2_CH2_P: U502.13 (SENSE2+); also elsewhere on the board
PM2_CH3_N: U502.7 (SENSE3-); also elsewhere on the board
PM2_CH3_P: U502.8 (SENSE3+); also elsewhere on the board
PM2_CH4_N: U502.9 (SENSE4-); also elsewhere on the board
PM2_CH4_P: U502.10 (SENSE4+); also elsewhere on the board
PM3_CH1_N: U503.12 (SENSE1-); also elsewhere on the board
PM3_CH1_P: U503.11 (SENSE1+); also elsewhere on the board
PM3_CH2_N: U503.14 (SENSE2-); also elsewhere on the board
PM3_CH2_P: U503.13 (SENSE2+); also elsewhere on the board
PM3_CH3_N: U503.7 (SENSE3-); also elsewhere on the board
PM3_CH3_P: U503.8 (SENSE3+); also elsewhere on the board
PM3_CH4_N: U503.9 (SENSE4-); also elsewhere on the board
PM3_CH4_P: U503.10 (SENSE4+); also elsewhere on the board
PM_ALERT: R504.2, U501.15 (GPIO), U502.15 (GPIO), U503.15 (GPIO); also elsewhere on the board

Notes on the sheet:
PM1: CH1 VBUS_USER 20m (5 A FS), CH2 VBAT 20m (+-5 A, bidirectional), CH3 VSYS 20m (5 A), CH4 5V_SDR 50m (2 A) PM2: CH1 5V_LCD 50m (2 A), CH2 3V3_MCU 50m (2 A), CH3 3V3_SD 330m (300 mA), CH4 3V3_ETH 1R (100 mA) PM3: CH1 3V3_GPS 1R (100 mA), CH2 3V3_M1421 2.2R (45 mA), CH3 3V3_PERIPH 2.2R (45 mA), C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
